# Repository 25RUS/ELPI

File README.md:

# ELPI
Electronic Load Power Indicator

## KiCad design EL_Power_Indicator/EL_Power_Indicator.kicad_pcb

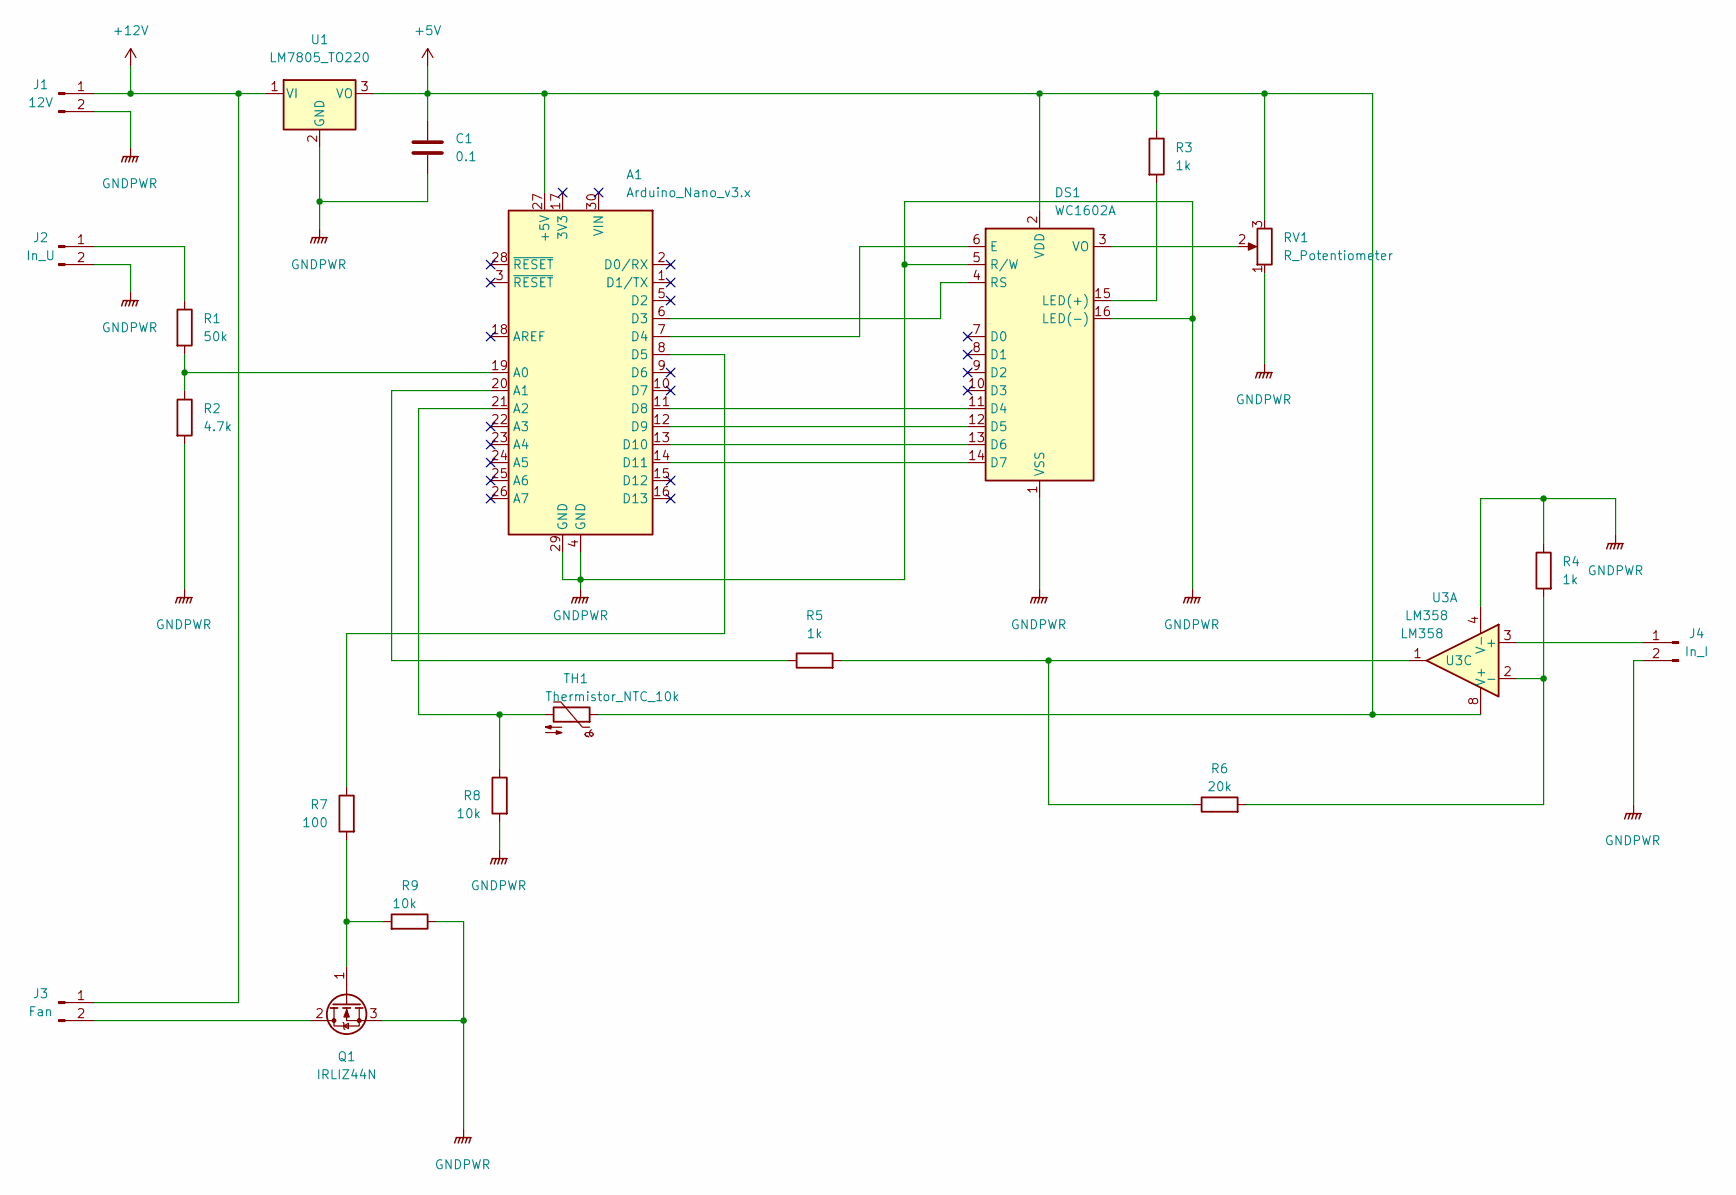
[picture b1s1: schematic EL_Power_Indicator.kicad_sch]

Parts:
A1: Arduino_Nano_v3.x; Arduino_Nano
C1: 0.1; C_Disc_D6.0mm_W4.4mm_P5.00mm
DS1: WC1602A
J1: 12V; JWT_A3963_1x02_P3.96mm_Vertical
J2: In_U; JWT_A3963_1x02_P3.96mm_Vertical
J3: Fan; JWT_A3963_1x02_P3.96mm_Vertical
J4: In_I; JWT_A3963_1x02_P3.96mm_Vertical
Q1: IRLIZ44N; TO-220F-3_Vertical
R1: 50k; R_Axial_DIN0309_L9.0mm_D3.2mm_P12.70mm_Horizontal
R2: 4.7k; R_Axial_DIN0309_L9.0mm_D3.2mm_P12.70mm_Horizontal
R3, R4, R5: 1k; R_Axial_DIN0309_L9.0mm_D3.2mm_P12.70mm_Horizontal
R6: 20k; R_Axial_DIN0309_L9.0mm_D3.2mm_P12.70mm_Horizontal
R7: 100; R_Axial_DIN0309_L9.0mm_D3.2mm_P12.70mm_Horizontal
R8, R9: 10k; R_Axial_DIN0309_L9.0mm_D3.2mm_P12.70mm_Horizontal
RV1: R_Potentiometer; Potentiometer_ACP_CA6-H2,5_Horizontal
TH1: Thermistor_NTC_10k; JWT_A3963_1x02_P3.96mm_Vertical
U1: LM7805_TO220; TO-220-3_Vertical
U3: LM358; DIP-8_W7.62mm

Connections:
+5V: A1.27 (+5V), C1.1, DS1.2 (VDD), R3.1, RV1.3, TH1.1, U1.3 (VO), U3.8 (V+)
+12V: J1.1, J3.1, U1.1 (VI)
GNDPWR: A1.4 (GND), A1.29 (GND), C1.2, DS1.1 (VSS), DS1.5 (R/W), DS1.16 (LED(-)), J1.2, J2.2, J4.2, Q1.3 (S), R2.2, R4.1, R8.2, R9.1, RV1.1, U1.2 (GND), U3.4 (V-)
unnamed: A1.6 (D3), DS1.4 (RS)
unnamed: A1.7 (D4), DS1.6 (E)
unnamed: A1.8 (D5), R7.1
unnamed: A1.11 (D8), DS1.11 (D4)
unnamed: A1.12 (D9), DS1.12 (D5)
unnamed: A1.13 (D10), DS1.13 (D6)
unnamed: A1.14 (D11), DS1.14 (D7)
unnamed: A1.19 (A0), R1.2, R2.1
unnamed: A1.20 (A1), R5.1
unnamed: A1.21 (A2), R8.1, TH1.2
unnamed: J2.1, R1.1
unnamed: J3.2, Q1.2 (D)
unnamed: J4.1, U3.3 (+)
unnamed: Q1.1 (G), R7.2, R9.2
unnamed: DS1.15 (LED(+)), R3.2
unnamed: R4.2, R6.2, U3.2 (-)
unnamed: R5.2, R6.1, U3.1
unnamed: DS1.3 (VO), RV1.2

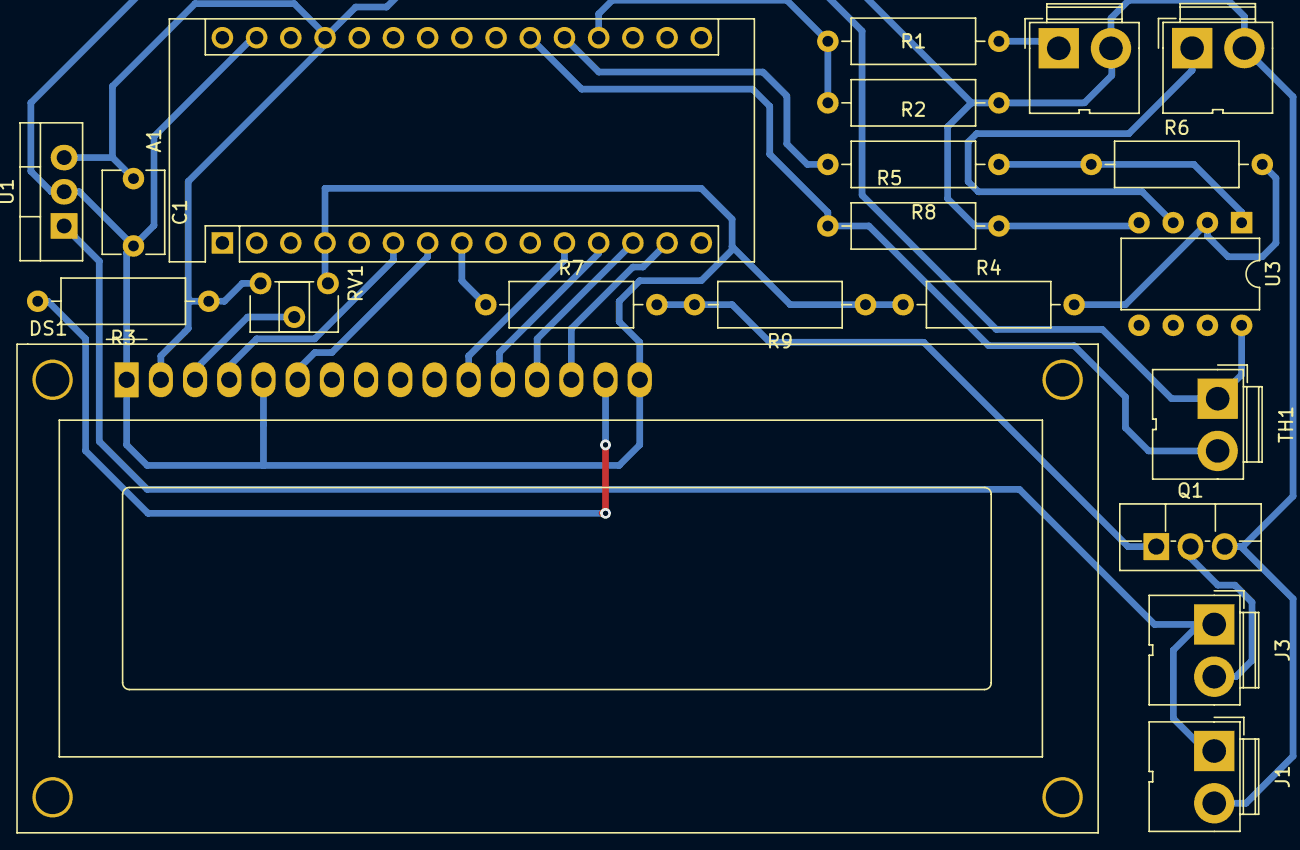
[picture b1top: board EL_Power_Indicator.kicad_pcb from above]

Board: 2 copper layers, 21 parts (0 on the bottom side), 21 nets.

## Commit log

2023-01-21 init
